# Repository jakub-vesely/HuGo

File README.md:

Main goal of this project is to build a robotic car for my children. Although, it is designed as a common modular system with ambition to be used as a generic educative tool/toy.

Current version is based on ESP32, and Micropython. Extensive blocks (tyny-blocks) are based on AtTiny 412/416 microcontrollers running Arduino code.

project use forked Micropython https://github.com/jakub-vesely/micropython. HuGo board specific code is placed in the micropython/ports/esp32/boards/HUGO/ directory
and can be flashed by command: idf.py -D MICROPY_BOARD=HUGO -B build-HUGO flash monitor -p <COM PORT>

Python code can be build to the firmware by placing to  /ports/esp32/boards/HUGO/modules
or added by tools/ble_cient.py (code is uplodated wireless via BLE)

## Sources
* Overview of ESP32 features is available here: https://www.espressif.com/en/products/socs/esp32/overview
* esp-idf is linked externaly as recommended. Getting started guide is available here: https://docs.espressif.com/projects/esp-idf/en/stable/get-started/
* Arduino official web page https://www.arduino.cc/
* Arduino suport for AtTiny series 0 and 1 https://github.com/SpenceKonde/megaTinyCore

## Deprecated
* originally was the HuGo project based of LUA but this interpreter is not supported any more
* esp-idf project with LUA support has been moved to src_depricated directory
* LUA 3.5.4 is part of the repository. Original source code is available here: https://www.lua.org/download.html

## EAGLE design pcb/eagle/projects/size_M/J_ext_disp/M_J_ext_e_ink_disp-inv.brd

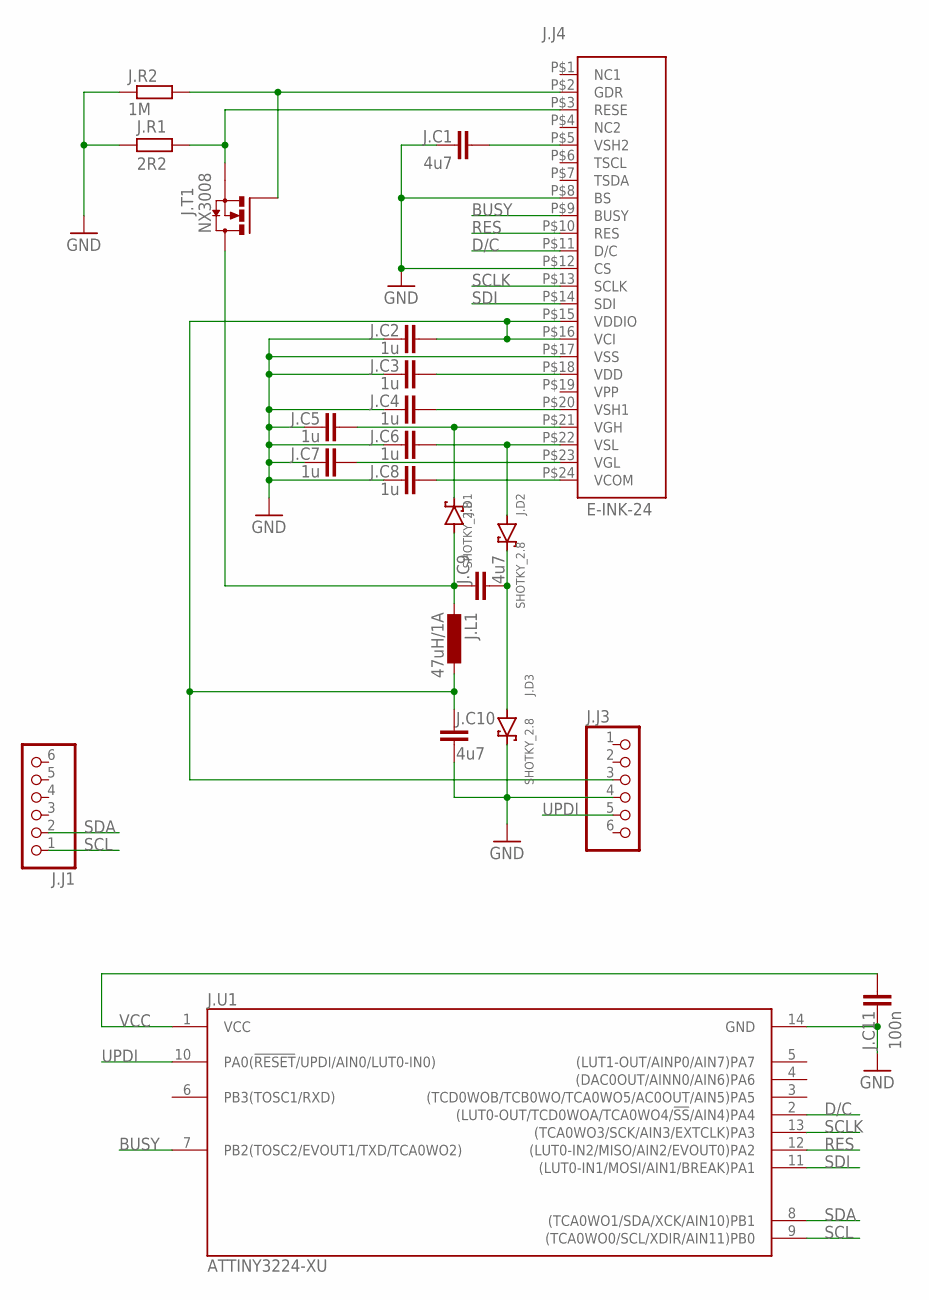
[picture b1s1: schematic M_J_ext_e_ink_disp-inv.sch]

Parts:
J.C1, J.C9, J.C10: 4u7; C0603
J.C2, J.C3, J.C4, J.C5, J.C6, J.C7, J.C8: 1u; C0603
J.C11: 100n; C0603
J.D1, J.D2, J.D3: SHOTKY_2.8
J.J1, J.J3: PINHD-1X6; 1X06
J.J4: E-INK-24
J.L1: 47uH/1A; L3230M
J.R1: 2R2; R0603
J.R2: 1M; R0603
J.T1: NX3008; SO23
J.U1: ATTINY3224-XU; TSSOP14

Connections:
BUSY: J.J4.P$9 (BUSY), J.U1.7 (PB2(TOSC2/EVOUT1/TXD/TCA0WO2))
D/C: J.J4.P$11 (D/C), J.U1.2 ((LUT0-OUT/TCD0WOA/TCA0WO4/!SS!/AIN4)PA4)
GND: J.C1.2, J.C2.2, J.C3.2, J.C4.2, J.C5.2, J.C6.2, J.C7.2, J.C8.2, J.C10.2, J.C11.2, J.D3.K (C), J.J3.4, J.J4.P$8 (BS), J.J4.P$12 (CS), J.J4.P$17 (VSS), J.R1.2, J.R2.1, J.U1.14 (GND)
unnamed: J.C1.1, J.J4.P$5 (VSH2)
unnamed: J.C8.1, J.J4.P$24 (VCOM)
unnamed: J.C6.1, J.D2.A, J.J4.P$22 (VSL)
unnamed: J.C5.1, J.D1.K (C), J.J4.P$21 (VGH)
unnamed: J.C9.2, J.D2.K (C), J.D3.A
unnamed: J.J4.P$3 (RESE), J.R1.1, J.T1.S
unnamed: J.C3.1, J.J4.P$18 (VDD)
unnamed: J.C4.1, J.J4.P$20 (VSH1)
unnamed: J.C9.1, J.D1.A, J.L1.2, J.T1.D
unnamed: J.C7.1, J.J4.P$23 (VGL)
unnamed: J.J4.P$2 (GDR), J.R2.2, J.T1.G
RES: J.J4.P$10 (RES), J.U1.12 ((LUT0-IN2/MISO/AIN2/EVOUT0)PA2)
SCL: J.J1.1, J.U1.9 ((TCA0WO0/SCL/XDIR/AIN11)PB0)
SCLK: J.J4.P$13 (SCLK), J.U1.13 ((TCA0WO3/SCK/AIN3/EXTCLK)PA3)
SDA: J.J1.2, J.U1.8 ((TCA0WO1/SDA/XCK/AIN10)PB1)
SDI: J.J4.P$14 (SDI), J.U1.11 ((LUT0-IN1/MOSI/AIN1/BREAK)PA1)
UPDI: J.J3.5, J.U1.10 (PA0(!RESET!/UPDI/AIN0/LUT0-IN0))
VCC: J.C2.1, J.C10.1, J.C11.1, J.J3.3, J.J4.P$15 (VDDIO), J.J4.P$16 (VCI), J.L1.1, J.U1.1 (VCC)

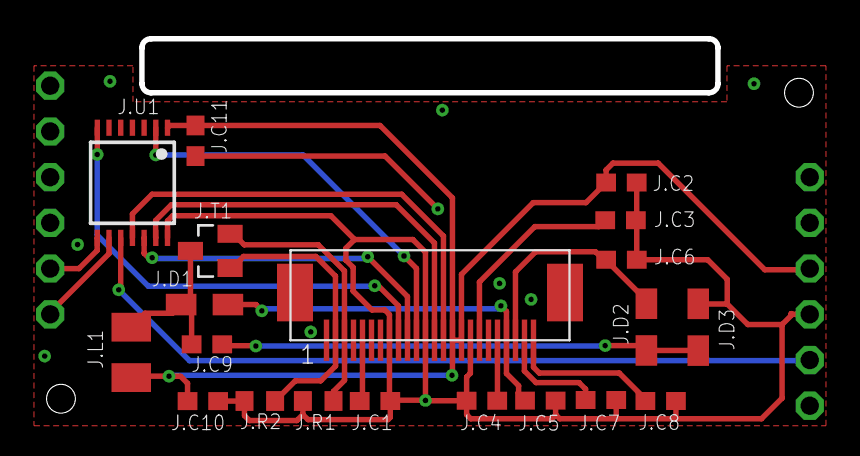
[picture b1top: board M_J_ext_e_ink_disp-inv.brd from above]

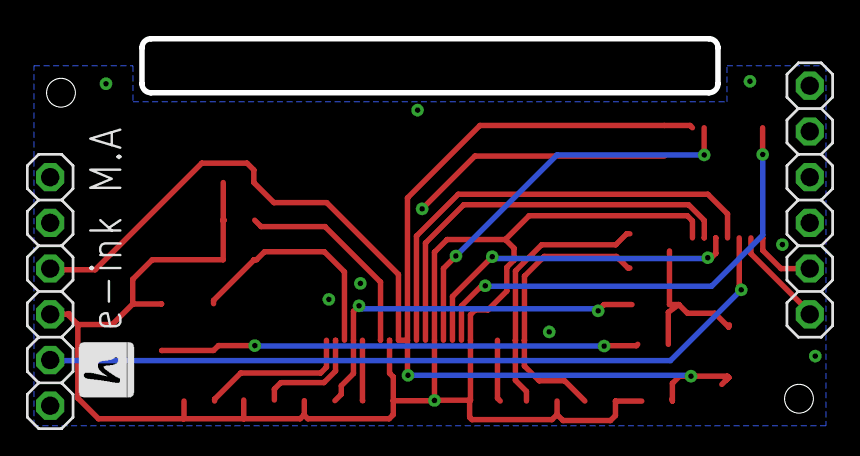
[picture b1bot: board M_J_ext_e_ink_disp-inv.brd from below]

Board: 2 copper layers, 32.0 x 3.0 mm, 22 parts (2 on the bottom side), 21 nets.

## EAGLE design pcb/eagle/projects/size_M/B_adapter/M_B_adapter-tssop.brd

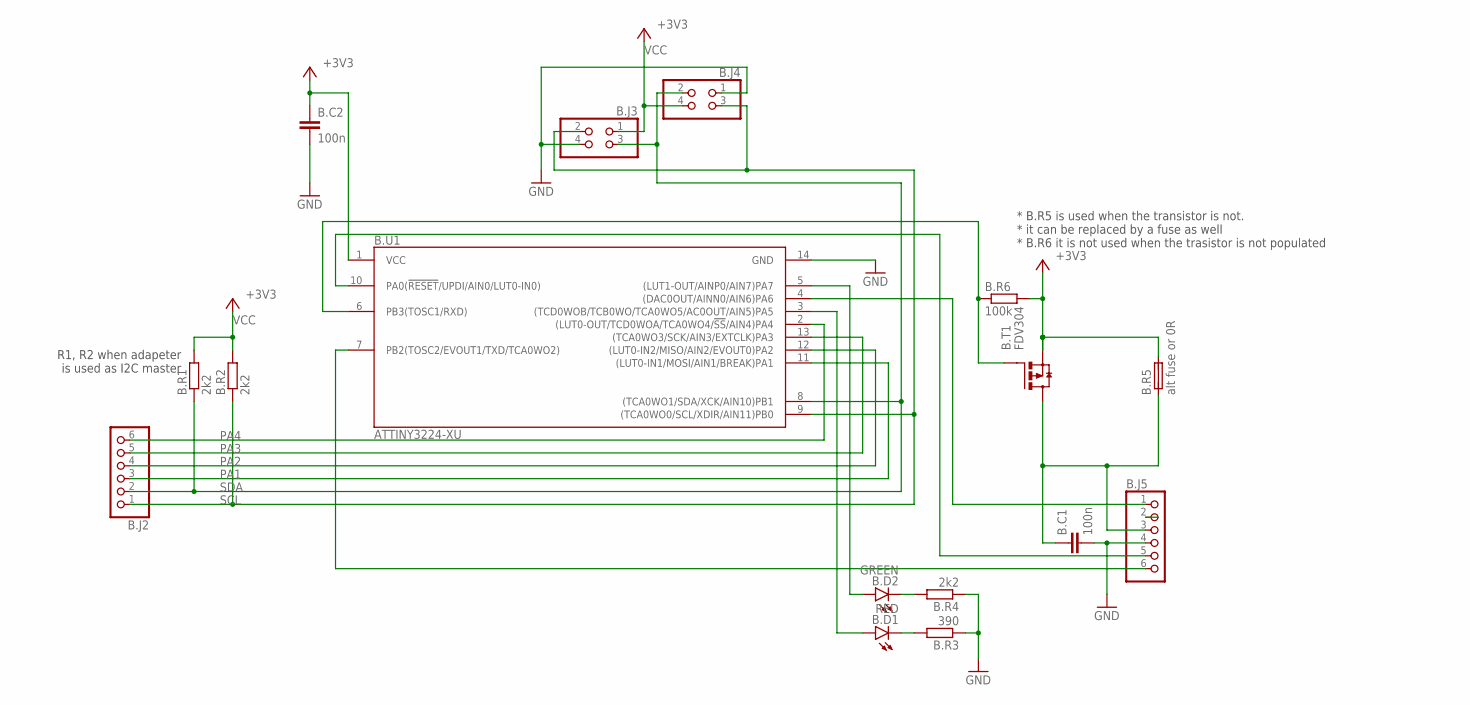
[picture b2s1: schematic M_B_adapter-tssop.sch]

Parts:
B.C1, B.C2: 100n; C0603
B.D1: RED; CHIP-LED0603
B.D2: GREEN; CHIP-LED0603
B.J2, B.J5: PINHD-1X6; 1X06
B.J3, B.J4: PINHD-2X2; 2X02
B.R1, B.R2, B.R4: 2k2; R0603
B.R3: 390; R0603
B.R5: alt fuse or 0R; FUSE
B.R6: 100k; R0603
B.T1: FDV304; SO23
B.U1: ATTINY3224-XU; TSSOP14

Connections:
GND: B.C1.2, B.C2.2, B.J3.4, B.J4.1, B.J5.4, B.R3.1, B.R4.1, B.U1.14 (GND)
unnamed: B.D2.C1 (C), B.R4.2
unnamed: B.D1.C1 (C), B.R3.2
unnamed: B.C1.1, B.J5.3, B.R5.1, B.T1.D
unnamed: B.D1.A1 (A), B.U1.3 ((TCD0WOB/TCB0WO/TCA0WO5/AC0OUT/AIN5)PA5)
PA1: B.J2.3, B.U1.11 ((LUT0-IN1/MOSI/AIN1/BREAK)PA1)
PA2: B.J2.4, B.U1.12 ((LUT0-IN2/MISO/AIN2/EVOUT0)PA2)
PA3: B.J2.5, B.U1.13 ((TCA0WO3/SCK/AIN3/EXTCLK)PA3)
PA4: B.J2.6, B.U1.2 ((LUT0-OUT/TCD0WOA/TCA0WO4/!SS!/AIN4)PA4)
PA6: B.J5.1, B.U1.4 ((DAC0OUT/AINN0/AIN6)PA6)
PA7: B.D2.A1 (A), B.U1.5 ((LUT1-OUT/AINP0/AIN7)PA7)
PB2: B.J5.6, B.U1.7 (PB2(TOSC2/EVOUT1/TXD/TCA0WO2))
PB3: B.R6.1, B.T1.G, B.U1.6 (PB3(TOSC1/RXD))
SCL: B.J2.1, B.J3.2, B.J4.3, B.R2.1, B.U1.9 ((TCA0WO0/SCL/XDIR/AIN11)PB0)
SDA: B.J2.2, B.J3.3, B.J4.2, B.R1.1, B.U1.8 ((TCA0WO1/SDA/XCK/AIN10)PB1)
UPDI: B.J5.5, B.U1.10 (PA0(!RESET!/UPDI/AIN0/LUT0-IN0))
VBAT: B.J5.2
VCC: B.C2.1, B.J3.1, B.J4.4, B.R1.2, B.R2.2, B.R5.2, B.R6.2, B.T1.S, B.U1.1 (VCC)

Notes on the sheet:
* B.R5 is used when the transistor is not. * it can be replaced by a fuse as well * B.R6 it is not used when the trasistor is not populated
R1, R2 when adapeter is used as I2C master

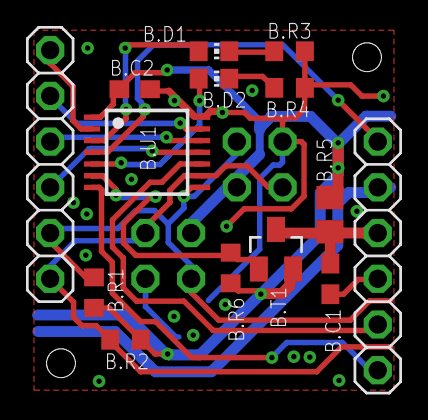
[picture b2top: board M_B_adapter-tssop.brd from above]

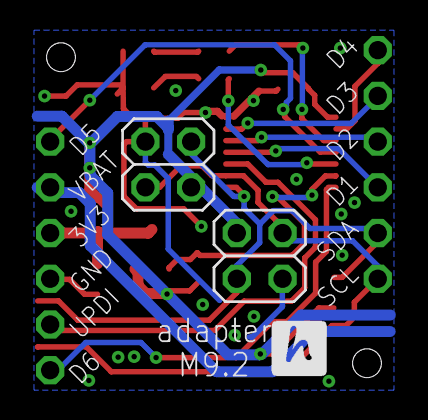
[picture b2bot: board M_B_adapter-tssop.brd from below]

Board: 2 copper layers, 16 parts (2 on the bottom side), 17 nets.

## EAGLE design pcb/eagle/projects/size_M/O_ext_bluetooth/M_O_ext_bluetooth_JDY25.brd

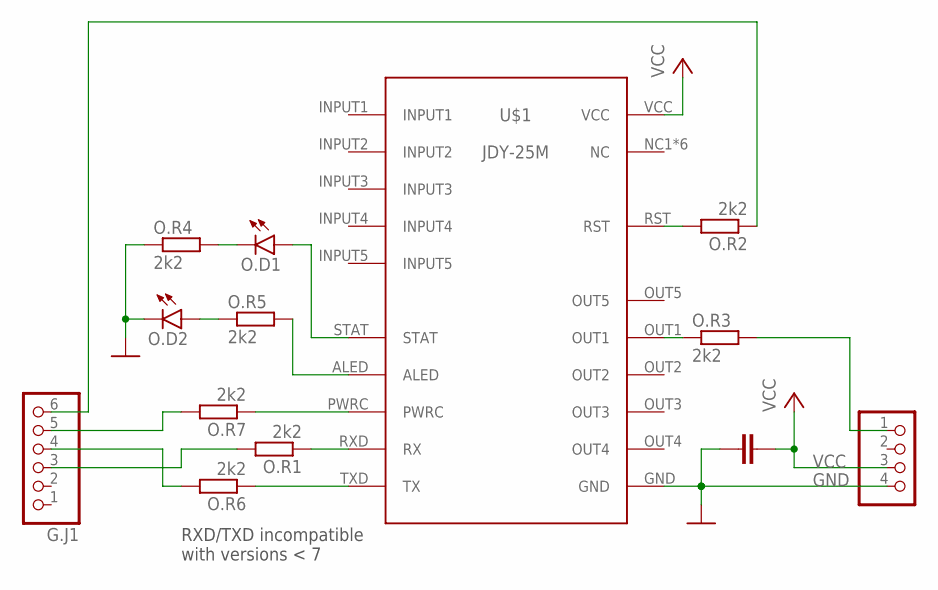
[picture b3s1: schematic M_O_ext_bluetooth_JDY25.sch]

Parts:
G.J1: PINHD-1X6; 1X06
G.J2: PINHD-1X4; 1X04
O.C1: 100n; C0603
O.D1, O.D2: LEDCHIP-LED0603; CHIP-LED0603
O.R1, O.R2, O.R3, O.R4, O.R5, O.R6, O.R7: 2k2; R0603
U$1: JDY-25

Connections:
GND: G.J2.4, O.C1.1, O.D2.C1 (C), O.R4.1, U$1.GND
unnamed: O.R1.1, U$1.RXD (RX)
unnamed: O.R6.1, U$1.TXD (TX)
unnamed: G.J1.5, O.R7.2
unnamed: O.R7.1, U$1.PWRC
unnamed: G.J2.1, O.R3.2
unnamed: O.R5.2, U$1.ALED
unnamed: O.D1.A1 (A), U$1.STAT
unnamed: G.J1.6, O.R2.1
unnamed: O.D1.C1 (C), O.R4.2
unnamed: O.D2.A1 (A), O.R5.1
unnamed: O.R3.1, U$1.OUT1
unnamed: O.R2.2, U$1.RST
RX: G.J1.4, O.R6.2
TX: G.J1.3, O.R1.2
VCC: G.J2.3, O.C1.2, U$1.VCC

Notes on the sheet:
RXD/TXD incompatible with versions < 7

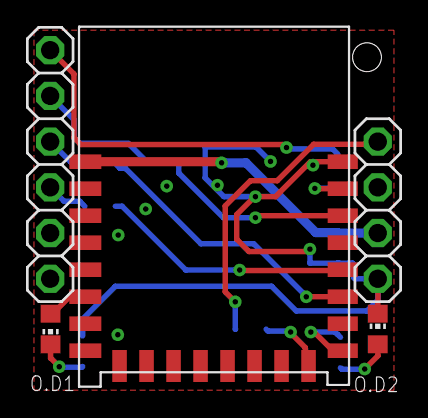
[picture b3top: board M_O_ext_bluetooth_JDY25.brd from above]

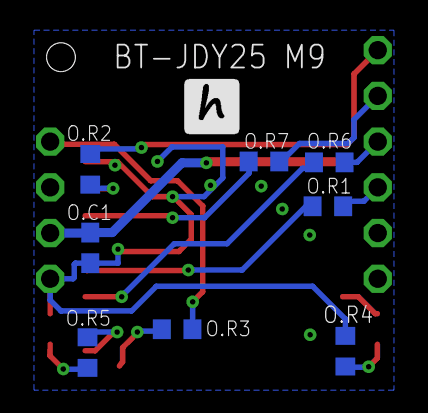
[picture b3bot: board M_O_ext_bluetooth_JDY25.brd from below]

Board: 2 copper layers, 13 parts (8 on the bottom side), 16 nets.

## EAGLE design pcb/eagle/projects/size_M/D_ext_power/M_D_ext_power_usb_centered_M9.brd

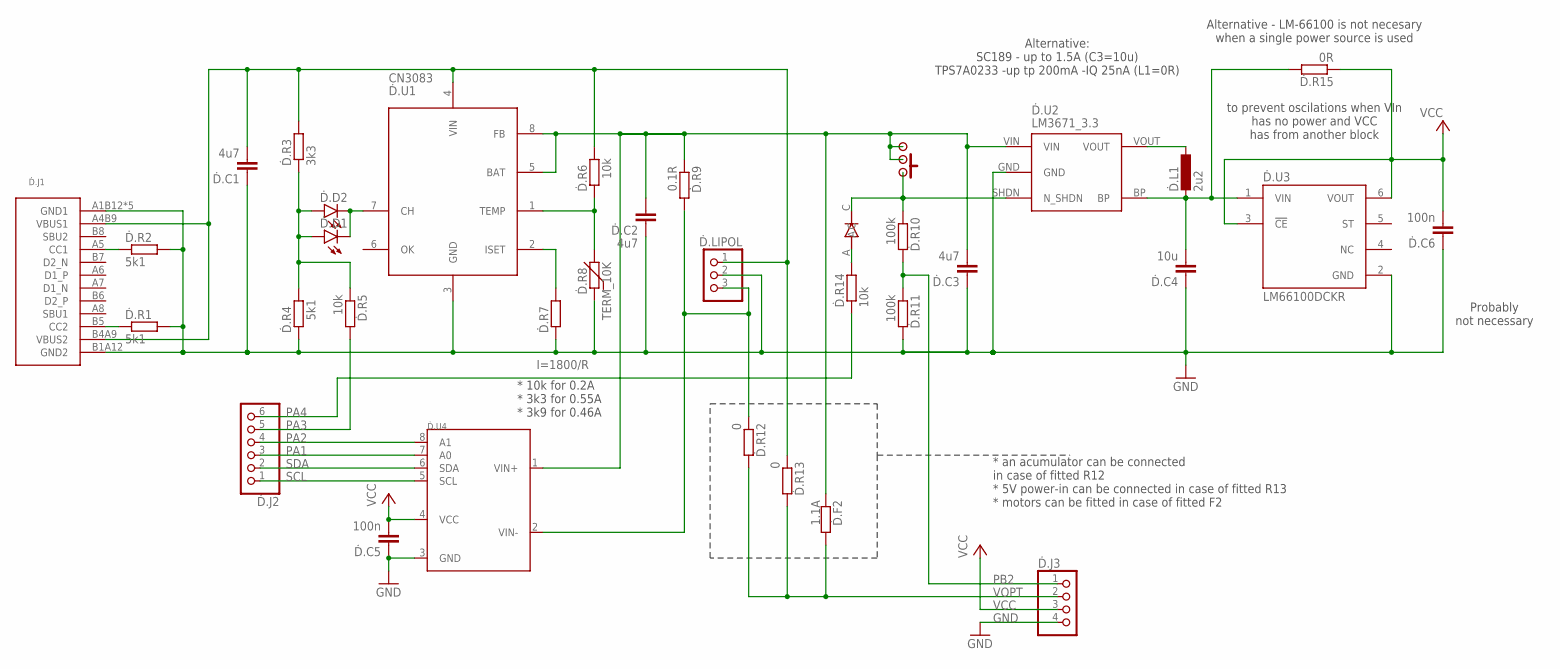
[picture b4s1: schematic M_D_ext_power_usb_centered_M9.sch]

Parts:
Ḋ.BTN: SWITCH
Ḋ.C1, Ḋ.C2, Ḋ.C3: 4u7; C0603
Ḋ.C4: 10u; C0603
Ḋ.C5, Ḋ.C6: 100n; C0603
Ḋ.D1, Ḋ.D2: LEDCHIP-LED0603; CHIP-LED0603
Ḋ.D3: DIODE
Ḋ.F2: 1.1A; R0805
Ḋ.J1: USB-C
Ḋ.J2: PINHD-1X6; 1X06
Ḋ.J3: PINHD-1X4; 1X04
Ḋ.L1: 2u2; L3230M
Ḋ.LIPOL: PINHEAD-1X3-2; 1X-03-2
Ḋ.R1, Ḋ.R2, Ḋ.R4: 5k1; R0603
Ḋ.R3: 3k3; R0603
Ḋ.R5, Ḋ.R6, Ḋ.R14: 10k; R0603
Ḋ.R7: I=1800/R; R0603
Ḋ.R8: TERM_10K; THERM
Ḋ.R9: 0.1R; R0805
Ḋ.R10, Ḋ.R11: 100k; R0603
Ḋ.R12, Ḋ.R13: 0; R0603
Ḋ.R15: 0R; R0603
Ḋ.U1: CN3083; SOP8
Ḋ.U2: LM3671_3.3; SOT32-5
Ḋ.U3: LM66100DCKR; SOT65P210X110-6N
Ḋ.U4: INA219; SOT23-8

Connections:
5V: Ḋ.C1.2, Ḋ.J1.A4B9 (VBUS1), Ḋ.J1.B4A9 (VBUS2), Ḋ.LIPOL.1, Ḋ.R3.2, Ḋ.R6.2, Ḋ.R13.1, Ḋ.U1.4 (VIN)
CHRG: Ḋ.D1.A1 (A), Ḋ.D2.A1 (A), Ḋ.R3.1, Ḋ.R4.2, Ḋ.R5.1
GND: Ḋ.C1.1, Ḋ.C2.1, Ḋ.C3.1, Ḋ.C4.1, Ḋ.C5.1, Ḋ.C6.1, Ḋ.J1.A1B12 (GND1), Ḋ.J1.B1A12 (GND2), Ḋ.J1.SH1 (GND1), Ḋ.J1.SH2 (GND1), Ḋ.J1.SH3 (GND1), Ḋ.J1.SH4 (GND1), Ḋ.J3.4, Ḋ.LIPOL.2, Ḋ.R1.2, Ḋ.R2.2, Ḋ.R4.1, Ḋ.R7.1, Ḋ.R8.1, Ḋ.R11.2, Ḋ.U1.3 (GND), Ḋ.U2.GND, Ḋ.U3.2 (GND), Ḋ.U4.3 (GND)
IN+: Ḋ.BTN.P$2, Ḋ.BTN.P$3, Ḋ.BTN.P$4, Ḋ.BTN.P$6, Ḋ.C2.2, Ḋ.C3.2, Ḋ.F2.1, Ḋ.R9.1, Ḋ.U1.5 (BAT), Ḋ.U1.8 (FB), Ḋ.U2.VIN, Ḋ.U4.1 (VIN+)
IN-: Ḋ.LIPOL.3, Ḋ.R9.2, Ḋ.R12.1, Ḋ.U4.2 (VIN-)
unnamed: Ḋ.L1.1, Ḋ.U2.VOUT
unnamed: Ḋ.D1.C1 (C), Ḋ.D2.C1 (C), Ḋ.U1.7 (CH)
unnamed: Ḋ.J1.B5 (CC2), Ḋ.R1.1
unnamed: Ḋ.D3.A, Ḋ.R14.2
unnamed: Ḋ.J1.A5 (CC1), Ḋ.R2.1
unnamed: Ḋ.R7.2, Ḋ.U1.2 (ISET)
unnamed: Ḋ.R6.1, Ḋ.R8.2, Ḋ.U1.1 (TEMP)
unnamed: Ḋ.BTN.P$1, Ḋ.BTN.P$5, Ḋ.BTN.P$7, Ḋ.D3.C, Ḋ.R10.1, Ḋ.U2.SHDN (N_SHDN)
PA1: Ḋ.J2.3, Ḋ.U4.7 (A0)
PA2: Ḋ.J2.4, Ḋ.U4.8 (A1)
PA3: Ḋ.J2.5, Ḋ.R5.2
PA4: Ḋ.J2.6, Ḋ.R14.1
PB2: Ḋ.J3.1, Ḋ.R10.2, Ḋ.R11.1
SCL: Ḋ.J2.1, Ḋ.U4.5 (SCL)
SDA: Ḋ.J2.2, Ḋ.U4.6 (SDA)
VCC: Ḋ.C5.2, Ḋ.C6.2, Ḋ.J3.3, Ḋ.R15.1, Ḋ.U3.3 (!CE), Ḋ.U3.6 (VOUT), Ḋ.U4.4 (VCC)
VCC1: Ḋ.C4.2, Ḋ.L1.2, Ḋ.R15.2, Ḋ.U2.BP, Ḋ.U3.1 (VIN)
VOPT: Ḋ.F2.2, Ḋ.J3.2, Ḋ.R12.2, Ḋ.R13.2

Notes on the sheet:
* an acumulator can be connected in case of fitted R12 * 5V power-in can be connected in case of fitted R13 * motors can be fitted in case of fitted F2
to prevent oscilations when VIn has no power and VCC has from another block
* 10k for 0.2A * 3k3 for 0.55A * 3k9 for 0.46A
Alternative: SC189 - up to 1.5A (C3=10u) TPS7A0233 -up tp 200mA -IQ 25nA (L1=0R)
Probably not necessary
Alternative - LM-66100 is not necesary when a single power source is used

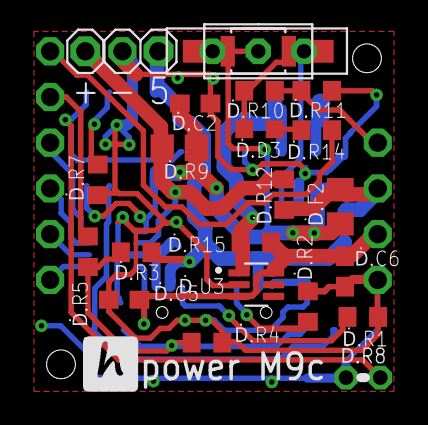
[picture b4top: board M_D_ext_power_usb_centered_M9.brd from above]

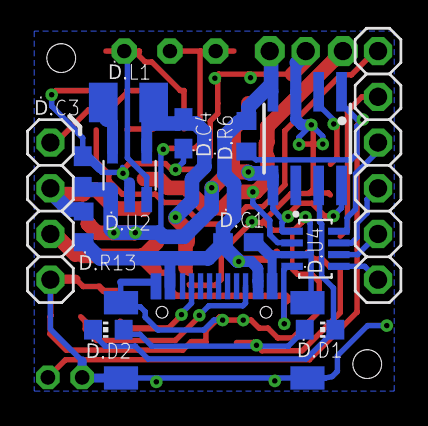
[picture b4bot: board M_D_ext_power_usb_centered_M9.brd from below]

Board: 2 copper layers, 35 parts (14 on the bottom side), 23 nets.

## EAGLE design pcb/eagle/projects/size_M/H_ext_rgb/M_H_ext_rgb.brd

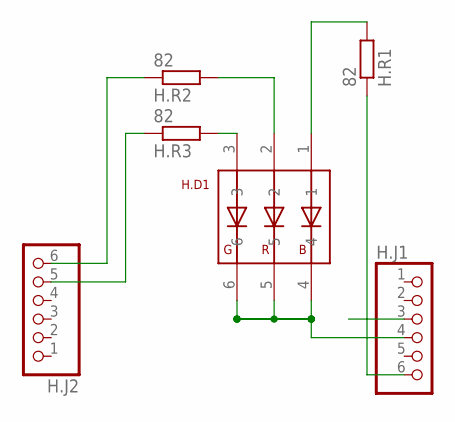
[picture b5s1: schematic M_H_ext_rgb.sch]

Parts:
H.D1: RGB_WW-FCE50TC-Q1
H.J1, H.J2: PINHD-1X6; 1X06
H.R1, H.R2, H.R3: 82; R0603

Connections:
GND: H.D1.4, H.D1.5, H.D1.6, H.J1.4
unnamed: H.D1.1, H.R1.2
unnamed: H.D1.3, H.R3.2
unnamed: H.D1.2, H.R2.2
unnamed: H.J1.6, H.R1.1
unnamed: H.J2.6, H.R2.1
unnamed: H.J2.5, H.R3.1
VDD: H.J1.3

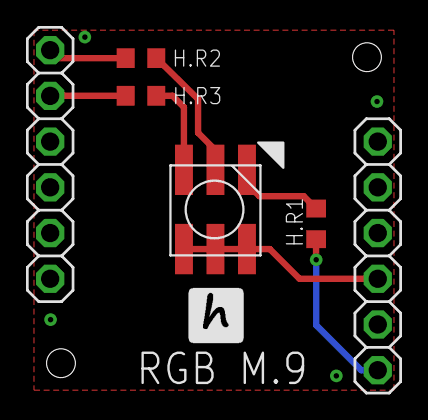
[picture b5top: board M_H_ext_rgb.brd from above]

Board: 2 copper layers, 6 parts (0 on the bottom side), 7 nets.

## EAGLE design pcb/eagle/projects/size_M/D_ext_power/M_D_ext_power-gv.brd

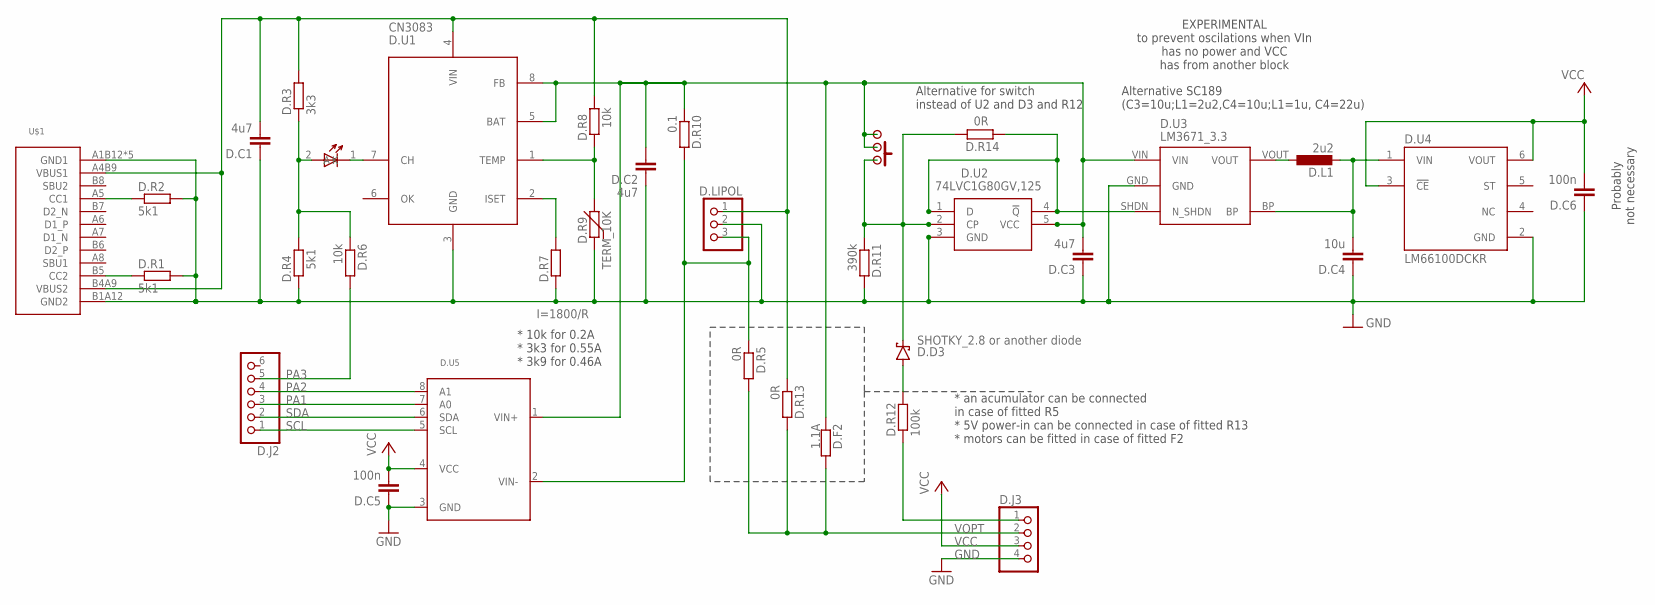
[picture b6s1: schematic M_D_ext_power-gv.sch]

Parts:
D.C1, D.C2, D.C3: 4u7; C0603
D.C4: 10u; C0603
D.C5, D.C6: 100n; C0603
D.D1: LED_1.8
D.D3: SHOTKY_2.8 or another diode; SHOTKY_2.8
D.F2: 1.1A; R0805
D.J2: PINHD-1X6; 1X06
D.J3: PINHD-1X4; 1X04
D.L1: 2u2; L3230M
D.LIPOL: PINHEAD-1X3-2; 1X-03-2
D.ON/OFF/RESET: SWITCH
D.R1, D.R2, D.R4: 5k1; R0603
D.R3: 3k3; R0603
D.R5, D.R13, D.R14: 0R; R0603
D.R6, D.R8: 10k; R0603
D.R7: I=1800/R; R0603
D.R9: TERM_10K; THERM
D.R10: 0.1; R0805
D.R11: 390k; R0603
D.R12: 100k; R0603
D.U1: CN3083; SOP8
D.U2: 74LVC1G80GV,125; SOT95P275X110-5N
D.U3: LM3671_3.3; SOT32-5
D.U4: LM66100DCKR; SOT65P210X110-6N
D.U5: INA219; SOT23-8
U$1: USB-C

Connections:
5V: D.C1.2, D.LIPOL.1, D.R3.2, D.R8.2, D.R13.1, D.U1.4 (VIN), U$1.A4B9 (VBUS1), U$1.B4A9 (VBUS2)
CHRG: D.D1.2 (A), D.R3.1, D.R4.2, D.R6.1
GND: D.C1.1, D.C2.1, D.C3.1, D.C4.1, D.C5.1, D.C6.1, D.J3.4, D.LIPOL.2, D.R1.2, D.R2.2, D.R4.1, D.R7.1, D.R9.1, D.R11.2, D.U1.3 (GND), D.U2.3 (GND), D.U3.GND, D.U4.2 (GND), D.U5.3 (GND), U$1.A1B12 (GND1), U$1.B1A12 (GND2), U$1.SH1 (GND1), U$1.SH2 (GND1), U$1.SH3 (GND1), U$1.SH4 (GND1)
IN+: D.C2.2, D.C3.2, D.F2.1, D.ON/OFF/RESET.P$2, D.ON/OFF/RESET.P$3, D.ON/OFF/RESET.P$4, D.ON/OFF/RESET.P$6, D.R10.1, D.U1.5 (BAT), D.U1.8 (FB), D.U2.5 (VCC), D.U3.VIN, D.U5.1 (VIN+)
IN-: D.LIPOL.3, D.R5.1, D.R10.2, D.U5.2 (VIN-)
unnamed: D.R14.1, D.U2.1 (D), D.U2.4 (!Q), D.U3.SHDN (N_SHDN)
unnamed: D.L1.1, D.U3.VOUT
unnamed: D.D1.1 (K), D.U1.7 (CH)
unnamed: D.R1.1, U$1.B5 (CC2)
unnamed: D.D3.A, D.R12.2
unnamed: D.R2.1, U$1.A5 (CC1)
unnamed: D.R7.2, D.U1.2 (ISET)
unnamed: D.R8.1, D.R9.2, D.U1.1 (TEMP)
unnamed: D.D3.K (C), D.ON/OFF/RESET.P$1, D.ON/OFF/RESET.P$5, D.ON/OFF/RESET.P$7, D.R11.1, D.R14.2, D.U2.2 (CP)
PA1: D.J2.3, D.U5.7 (A0)
PA2: D.J2.4, D.U5.8 (A1)
PA3: D.J2.5, D.R6.2
PA5-1: D.J3.1, D.R12.1
SCL: D.J2.1, D.U5.5 (SCL)
SDA: D.J2.2, D.U5.6 (SDA)
VCC: D.C5.2, D.C6.2, D.J3.3, D.U4.3 (!CE), D.U4.6 (VOUT), D.U5.4 (VCC)
VCC1: D.C4.2, D.L1.2, D.U3.BP, D.U4.1 (VIN)
VOPT: D.F2.2, D.J3.2, D.R5.2, D.R13.2

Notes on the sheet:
* an acumulator can be connected in case of fitted R5 * 5V power-in can be connected in case of fitted R13 * motors can be fitted in case of fitted F2
EXPERIMENTAL to prevent oscilations when VIn has no power and VCC has from another block
* 10k for 0.2A * 3k3 for 0.55A * 3k9 for 0.46A
Alternative SC189 (C3=10u;L1=2u2,C4=10u;L1=1u, C4=22u)
Probably not necessary
Alternative for switch instead of U2 and D3 and R12

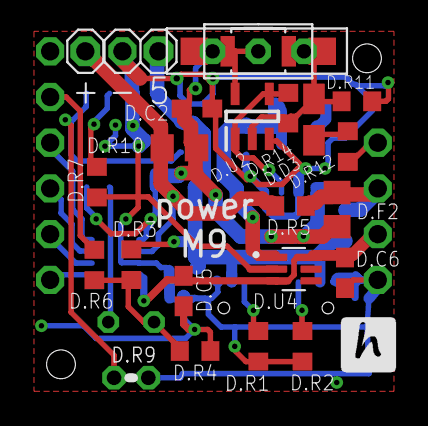
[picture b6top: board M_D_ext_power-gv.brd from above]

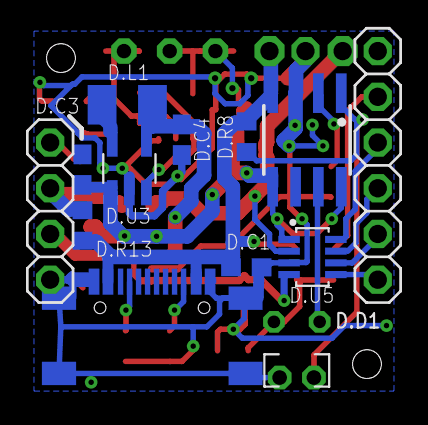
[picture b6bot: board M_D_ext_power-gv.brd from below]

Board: 2 copper layers, 34 parts (13 on the bottom side), 23 nets.

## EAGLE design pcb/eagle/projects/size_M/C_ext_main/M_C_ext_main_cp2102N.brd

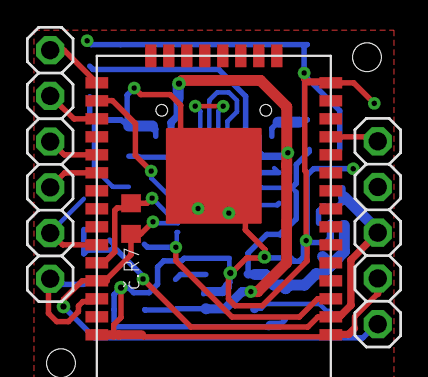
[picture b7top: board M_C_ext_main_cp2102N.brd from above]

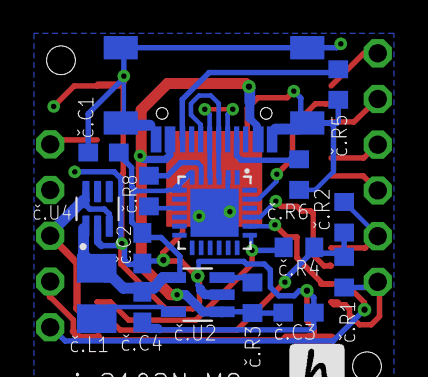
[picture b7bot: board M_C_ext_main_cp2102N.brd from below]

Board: 2 copper layers, 20 parts (16 on the bottom side), 23 nets.

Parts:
C.J2: 1X06
JP1: 1X05
U$1: USB-C
č.C1: 100n; C0603
č.C2: 4u7; C0603
č.C3: 4k7; C0603
č.C4: 10u; C0603
č.L1: 2u2; L3230M
č.R1, č.R2: 2k2; R0603
č.R3, č.R4: 100k; R0603
č.R5: 5K1; R0603
č.R6: 5k1; R0603
č.R7: 4k7; R0603
č.R8: 1k; R0603
č.U1: CP2102N; QFN50P400X400X80-25N
č.U2: LM3671_3.3; SOT32-5
č.U3: TTGO-MICRO-32
č.U4: LM66100DCKR; SOT65P210X110-6N

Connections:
GND: JP1.4, U$1.A1B12, U$1.B1A12, U$1.SH1, U$1.SH2, U$1.SH3, U$1.SH4, č.C1.1, č.C2.2, č.C3.1, č.C4.2, č.R5.1, č.R6.1, č.U1.2, č.U1.25, č.U2.GND, č.U3.GND1, č.U3.GND2, č.U3.GND3, č.U3.GND4, č.U3.GND5, č.U3.GND6, č.U3.GND7, č.U3.GND8, č.U3.GND9, č.U3.GND10, č.U3.GND11, č.U4.2
unnamed: U$1.A7, U$1.B7, č.U1.4
unnamed: U$1.A6, U$1.B6, č.U1.3
unnamed: U$1.A5, č.R6.2
unnamed: U$1.B5, č.R5.2
unnamed: C.J2.6, č.U3.IO2
unnamed: JP1.1, č.U3.IO27
unnamed: č.R8.2, č.U1.5
unnamed: č.L1.1, č.U2.VOUT
unnamed: č.R3.1, č.U2.SHDN
unnamed: C.J2.5, č.U3.IO4
unnamed: C.J2.4, č.U3.IO17
unnamed: C.J2.3, č.U3.IO5
unnamed: č.R8.1, č.U1.9
PROG: č.U1.23, č.U3.IO0
RESET: č.R4.1, č.U1.19, č.U3.EN
RX: JP1.5, č.R7.1, č.U1.20, č.U3.TXD0
SCL: C.J2.1, č.R1.1, č.U3.IO22
SDA: C.J2.2, č.R2.1, č.U3.IO21
TX: č.R7.2, č.U1.21, č.U3.RXD0
VCC: JP1.3, č.R1.2, č.R2.2, č.R4.2, č.U3.3V3, č.U4.3, č.U4.6
VCC1: č.C1.2, č.C2.1, č.C4.1, č.L1.2, č.U1.6, č.U1.7, č.U2.BP, č.U4.1
VUSB: U$1.A4B9, U$1.B4A9, č.C3.2, č.R3.2, č.U2.VIN

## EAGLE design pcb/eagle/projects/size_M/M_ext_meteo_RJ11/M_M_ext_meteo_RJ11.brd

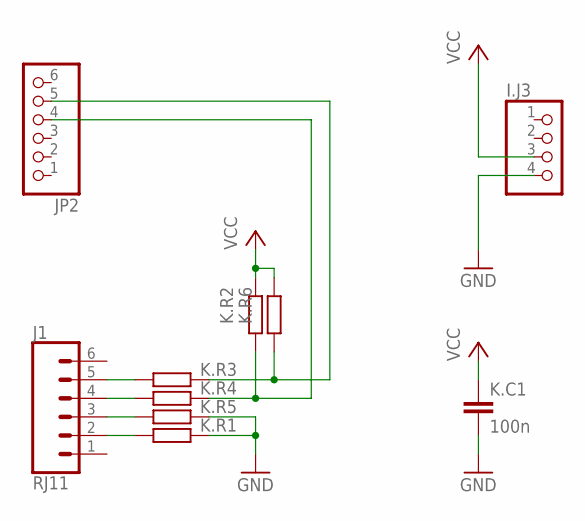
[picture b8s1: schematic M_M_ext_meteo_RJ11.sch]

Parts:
I.J3: PINHD-1X4; 1X04
J1: RJ11; RJ11-6
JP2: PINHD-1X6; 1X06
K.C1: 100n; C0603
K.R1, K.R3, K.R4, K.R5: 100; R0603
K.R2, K.R6: 10k; R0603

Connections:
GND: I.J3.4, K.C1.2, K.R1.1, K.R5.1
unnamed: J1.5, K.R3.2
unnamed: JP2.5, K.R3.1, K.R6.2
unnamed: JP2.4, K.R2.2, K.R4.1
unnamed: J1.4, K.R4.2
unnamed: J1.3, K.R5.2
unnamed: J1.2, K.R1.2
VCC: I.J3.3, K.C1.1, K.R2.1, K.R6.1

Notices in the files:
parts and their libraries:
SparkFun-Connectors: Licensing: Creative Commons ShareAlike 4.0 International - https://creativecommons.org/licenses/by-sa/4.0
